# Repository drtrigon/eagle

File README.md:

## Projekte

Results of eagle and kicad CI from travis are stored in https://github.com/drtrigon/eagle/tree/result/pcb branch and linked/shown in https://github.com/drtrigon/sketchbook repo. See there and in [.travis.yml](.travis.yml) for more info.

(might make sense to split projects off into separate repos/submodules)

### N64TinyUSB

Order: make sure to select PCB Thickness 2mm and "Gold Fingers"!

based on boxtec.ch Helvetiny 1.0 PCB design:
* https://github.com/boxtec/helvetiny85
* https://playground.boxtec.ch/doku.php/arduino/attinyusb/helvetiny85

#### code/firmware (design based on attiny45 n64-usb)

Built using the attiny45 n64-usb AVR source files. Works out of the box but emulates 1 device only (that contains both controller).

https://github.com/drtrigon/sketchbook/tree/master/cli/n64dual_tiny45

#### Hint: Order PCB directly

Upload the GERBER files below to https://jlcpcb.com/quote and order.

* Helvetiny85: https://github.com/drtrigon/eagle/blob/master/projects/HelveTiny_1.0_GERBER.zip
* Floweronly Arduino Shield: https://github.com/boxtec/floweronly/blob/master/floweronly_v1.0_GERBER.zip

### Drone_MultiWii / FlightController

### arduino-papilio_1-WireSniffer_Rev1

### DACRackUnit

## Setup

I would like to use features like CI (continous integration) keep a copy/mirror on e.g. github and more.

Maintaining a copy/mirror (more precise: with 2 remotes overloaded origin) on GitHub also allows
to use GitLab and GitHub together and by that all the nice featurs on GitHub.
See also; https://steveperkins.com/migrating-projects-from-github-to-gitlab/

"Option 2: Overload Origin with Both Remotes (needs one single pull/push only)"; in order to clone
and set this repo up use:
```
$ git clone file://///data/mount/gvfs/smb-share:server=.../01git/eagle.git
$ cd eagle
$ git remote set-url --add origin https://github.com/drtrigon/eagle.git
```
you can check the settings with:
```
$ git remote -v
origin  /data/mount/gvfs/smb-share:server=.../01git/eagle.git/ (fetch)
origin  /data/mount/gvfs/smb-share:server=.../01git/eagle.git/ (push)
origin  https://github.com/drtrigon/eagle.git (push)
```

### Enable EDRC.ME for a Repository (for Eagle)
http://www.edrc.me/docs/

### Enable Travis CI for a Repository (for Eagle)
https://github.com/drtrigon/test-eagle-edrc/blob/master/.travis.yml (does not work reliably yet)

Login to Travis-CI using the GitHub account and enable Travis-CI for the given repo.

Add a .travis.yml file to your project, commit, pull/push and enjoy.

A word of caution; the travis run will at the end - if successfull - try to push the
results back to this repo.

### Further Info
EDRC.me: https://michaelblouin.ca/blog/2018/02/25/automate-design-rule-checks-autodesk-eagle/

gerber (travis or local python script): http://www.rocketnumbernine.com/2011/12/14/automating-gerbers-from-eagle
```
...
# create top copper (cmp), bottom copper (sol), top solder mask (stc), bottom solder mask (sts), {top} silkscreen (plc)
${EAGLE} -X -dGERBER_RS274X -o${outputfile}.cmp ${board} Top Pads Vias
${EAGLE} -X -dGERBER_RS274X -o${outputfile}.sol ${board} Bottom Pads Vias
#${EAGLE} -X -dGERBER_RS274X -o${outputfile}.mil ${board} Milling
${EAGLE} -X -dGERBER_RS274X -o${outputfile}.plc ${board} Dimension tPlace tNames
${EAGLE} -X -dGERBER_RS274X -o${outputfile}.stc ${board} tStop
${EAGLE} -X -dGERBER_RS274X -o${outputfile}.sts ${board} bStop
#${EAGLE} -X -dGERBER_RS274X -o${outputfile}.crc ${board} tCream
#${EAGLE} -X -dGERBER_RS274X -o${outputfile}.dpv ${board} Drills
#${EAGLE} -X -dGERBER_RS274X -o${outputfile}.drh ${board} Holes
...
```
(mill and drill needs: gerb274x-mill-drill.cam)

#### Generate schematic, PCB and GERBER from KiCAD (TODO)
* https://forum.kicad.info/t/generate-gerber-files-from-script/1853/15
* https://electronics.stackexchange.com/questions/390135/command-line-interface-for-kicad

## License

The content of this project itself is licensed under the [Creative Commons Attribution 3.0 license](http://creativecommons.org/licenses/by/3.0/us/deed.en_US), and the underlying source code used to format and display that content is licensed under the [MIT license](http://opensource.org/licenses/mit-license.php), see the [LICENSE](LICENSE.md) file for license rights and limitations (MIT).

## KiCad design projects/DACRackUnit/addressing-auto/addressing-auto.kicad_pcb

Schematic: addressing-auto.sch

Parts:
C0, C1, C2, C3, C4: 100nF; C075-032X103
CP0: 10uF; B45181B
CPORT0: DIN-41651-20P
IC0, IC1, IC2, IC3: MC14585; PDIP-16
ICU0: MC14069; PDIP-14
PORT0, PORT1, PORT2, PORT3: DIN-41651-10P
R1, R2, R3, R4, R5, R6, R7, R8, R9, R10, R11, R12, R13, R14, R15, R16: 9k9; 0207_12
SP1: WAGO-3
SW0, SW1, SW2, SW3: 4pins; EDG-04

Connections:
+3V3: C0.1, C1.1, C2.1, C3.1, C4.1, CP0.+, IC0.VDD$16, IC1.VDD$16, IC2.VDD$16, IC3.VDD$16, ICU0.VDD$14, PORT0.P$6, PORT0.P$7, PORT1.P$6, PORT1.P$7, PORT2.P$6, PORT2.P$7, PORT3.P$6, PORT3.P$7, SP1.P$3, SW0.1, SW0.2, SW0.3, SW0.4, SW1.1, SW1.2, SW1.3, SW1.4, SW2.1, SW2.2, SW2.3, SW2.4, SW3.1, SW3.2, SW3.3, SW3.4
+5V: CPORT0.P$2, SP1.P$1
/B0.0: IC0.B0$11, R1.2, SW0.8
/B0.1: IC0.B1$9, R2.2, SW0.7
/B0.2: IC0.B2$1, R3.2, SW0.6
/B0.3: IC0.B3$14, R4.2, SW0.5
/B1.0: IC1.B0$11, R5.2, SW1.8
/B1.1: IC1.B1$9, R6.2, SW1.7
/B1.2: IC1.B2$1, R7.2, SW1.6
/B1.3: IC1.B3$14, R8.2, SW1.5
/B2.0: IC2.B0$11, R9.2, SW2.8
/B2.1: IC2.B1$9, R10.2, SW2.7
/B2.2: IC2.B2$1, R11.2, SW2.6
/B2.3: IC2.B3$14, R12.2, SW2.5
/B3.0: IC3.B0$11, R13.2, SW3.8
/B3.1: IC3.B1$9, R14.2, SW3.7
/B3.2: IC3.B2$1, R15.2, SW3.6
/B3.3: IC3.B3$14, R16.2, SW3.5
/CS: IC0.(A=B)_IN$6, IC1.(A=B)_IN$6, IC2.(A=B)_IN$6, IC3.(A=B)_IN$6, ICU0.OUT6$12
/CS0: IC0.(A=B)_OUT$3, ICU0.IN1$1
/CS0_INV: ICU0.OUT1$2, PORT0.P$1
/CS1: IC1.(A=B)_OUT$3, ICU0.IN2$3
/CS1_INV: ICU0.OUT2$4, PORT1.P$1
/CS2: IC2.(A=B)_OUT$3, ICU0.IN3$5
/CS2_INV: ICU0.OUT3$6, PORT2.P$1
/CS3: IC3.(A=B)_OUT$3, ICU0.IN4$9
/CS3_INV: ICU0.OUT4$8, PORT3.P$1
/CS_INV: CPORT0.P$13, ICU0.IN6$13
/P4: CPORT0.P$8, IC0.A0$10, IC1.A0$10, IC2.A0$10, IC3.A0$10
/P5: CPORT0.P$9, IC0.A1$7, IC1.A1$7, IC2.A1$7, IC3.A1$7
/P6: CPORT0.P$10, IC0.A2$2, IC1.A2$2, IC2.A2$2, IC3.A2$2
/P7: CPORT0.P$11, IC0.A3$15, IC1.A3$15, IC2.A3$15, IC3.A3$15
/RESET_INV: CPORT0.P$4, PORT0.P$9, PORT1.P$9, PORT2.P$9, PORT3.P$9
/SCLK: CPORT0.P$16, PORT0.P$2, PORT1.P$2, PORT2.P$2, PORT3.P$2
/SDIN: CPORT0.P$14, PORT0.P$4, PORT1.P$4, PORT2.P$4, PORT3.P$4
/SDO: CPORT0.P$15, PORT0.P$10, PORT1.P$10, PORT2.P$10, PORT3.P$10
GND: C0.2, C1.2, C2.2, C3.2, C4.2, CP0.-, CPORT0.P$1, IC0.(A<B)_IN$5, IC0.(A>B)_IN$4, IC0.VSS$8, IC1.(A<B)_IN$5, IC1.(A>B)_IN$4, IC1.VSS$8, IC2.(A<B)_IN$5, IC2.(A>B)_IN$4, IC2.VSS$8, IC3.(A<B)_IN$5, IC3.(A>B)_IN$4, IC3.VSS$8, ICU0.IN5$11, ICU0.VSS$7, PORT0.P$5, PORT1.P$5, PORT2.P$5, PORT3.P$5, R1.1, R2.1, R3.1, R4.1, R5.1, R6.1, R7.1, R8.1, R9.1, R10.1, R11.1, R12.1, R13.1, R14.1, R15.1, R16.1, SP1.P$2

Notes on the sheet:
GND
(+5 V)
P0.0
P0.4
P0.5
P0.6
P0.7
SPI CS 0
SPI MOSI (SDO)
SPI MISO (SDI)
SPI CLK (SCLK)
SYNC[inv]
DGND
LDAC[inv]
IOVCC
CLR[inv]
VCC_+5V
VDD_+3.3-4V
(GND = DGND only)
Flachkabel

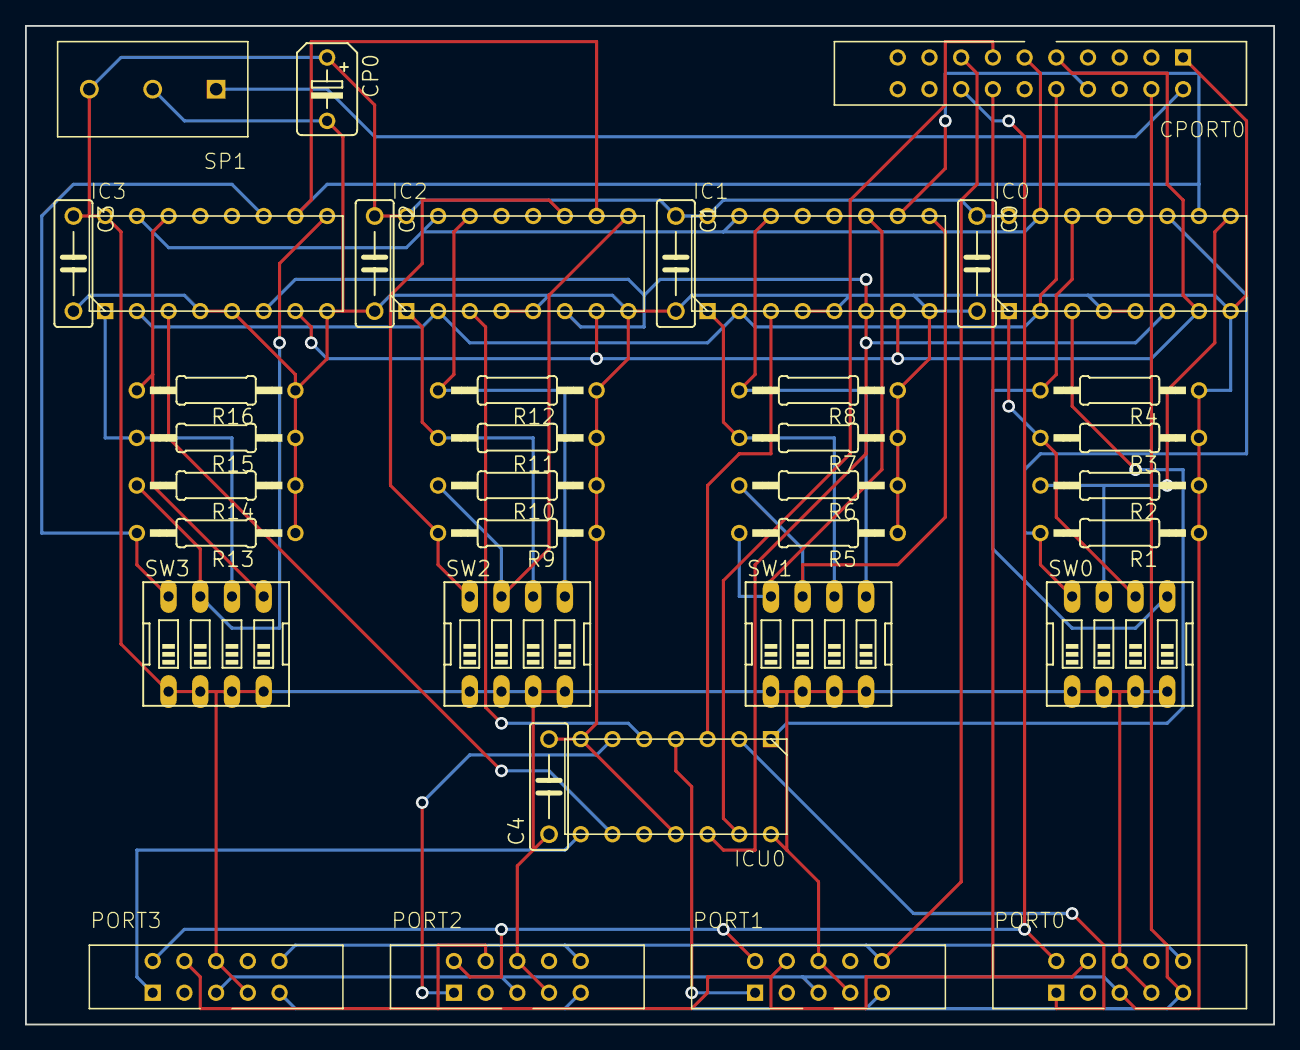
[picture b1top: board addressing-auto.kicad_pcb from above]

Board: 2 copper layers, 100.0 x 80.0 mm, 37 parts (0 on the bottom side), 37 nets.

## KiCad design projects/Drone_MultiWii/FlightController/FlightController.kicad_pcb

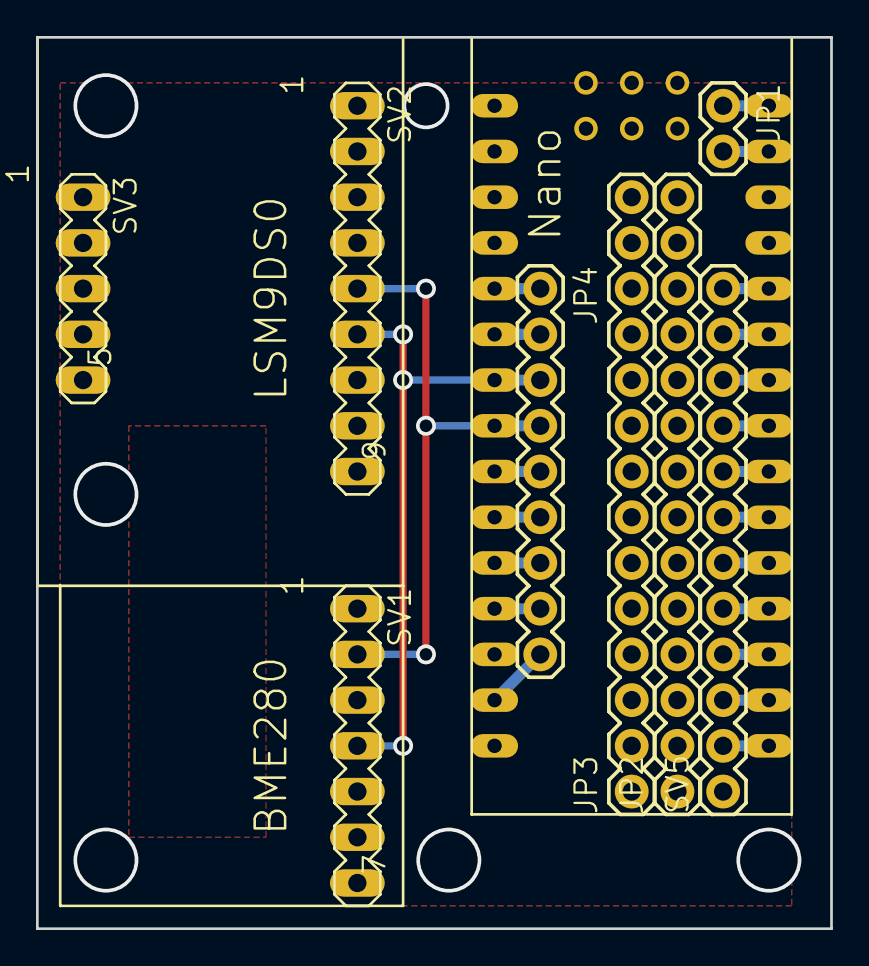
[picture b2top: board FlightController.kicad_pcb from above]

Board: 2 copper layers, 44.1 x 49.5 mm, 9 parts (0 on the bottom side), 24 nets.

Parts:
JP1: M02; 1X02
JP2, JP3: M14; 1X14
JP4: M09; 1X09
SV1: CON1; MA07-1
SV2: CON2; MA09-1
SV3: CON3; MA05-1
SV5: CON5; 1X12
U$1: NANO

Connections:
+5V: JP2.1, JP2.2, JP2.3, JP2.4, JP2.5, JP2.6, JP2.7, JP2.8, JP2.9, JP2.10, JP2.11, JP2.12, JP2.13, JP2.14, SV1.7, SV2.9, U$1.5V
GND: JP3.1, JP3.2, JP3.3, JP3.4, JP3.5, JP3.6, JP3.7, JP3.8, JP3.9, JP3.10, JP3.11, JP3.12, JP3.13, JP3.14, SV1.5, SV2.7, U$1.GND
unnamed: JP1.1, U$1.TX0
unnamed: JP1.2, U$1.RX1
unnamed: JP4.1, U$1.A7
unnamed: JP4.2, U$1.A6
unnamed: JP4.3, SV1.4, SV2.6, U$1.A5
unnamed: JP4.4, SV1.2, SV2.5, U$1.A4
unnamed: JP4.5, U$1.A3
unnamed: JP4.6, U$1.A2
unnamed: JP4.7, U$1.A1
unnamed: JP4.8, U$1.A0
unnamed: JP4.9, U$1.3.3V
unnamed: SV5.2, U$1.D12
unnamed: SV5.3, U$1.D11
unnamed: SV5.4, U$1.D10
unnamed: SV5.5, U$1.D9
unnamed: SV5.6, U$1.D8
unnamed: SV5.7, U$1.D7
unnamed: SV5.8, U$1.D6
unnamed: SV5.9, U$1.D5
unnamed: SV5.10, U$1.D4
unnamed: SV5.11, U$1.D3
unnamed: SV5.12, U$1.D2

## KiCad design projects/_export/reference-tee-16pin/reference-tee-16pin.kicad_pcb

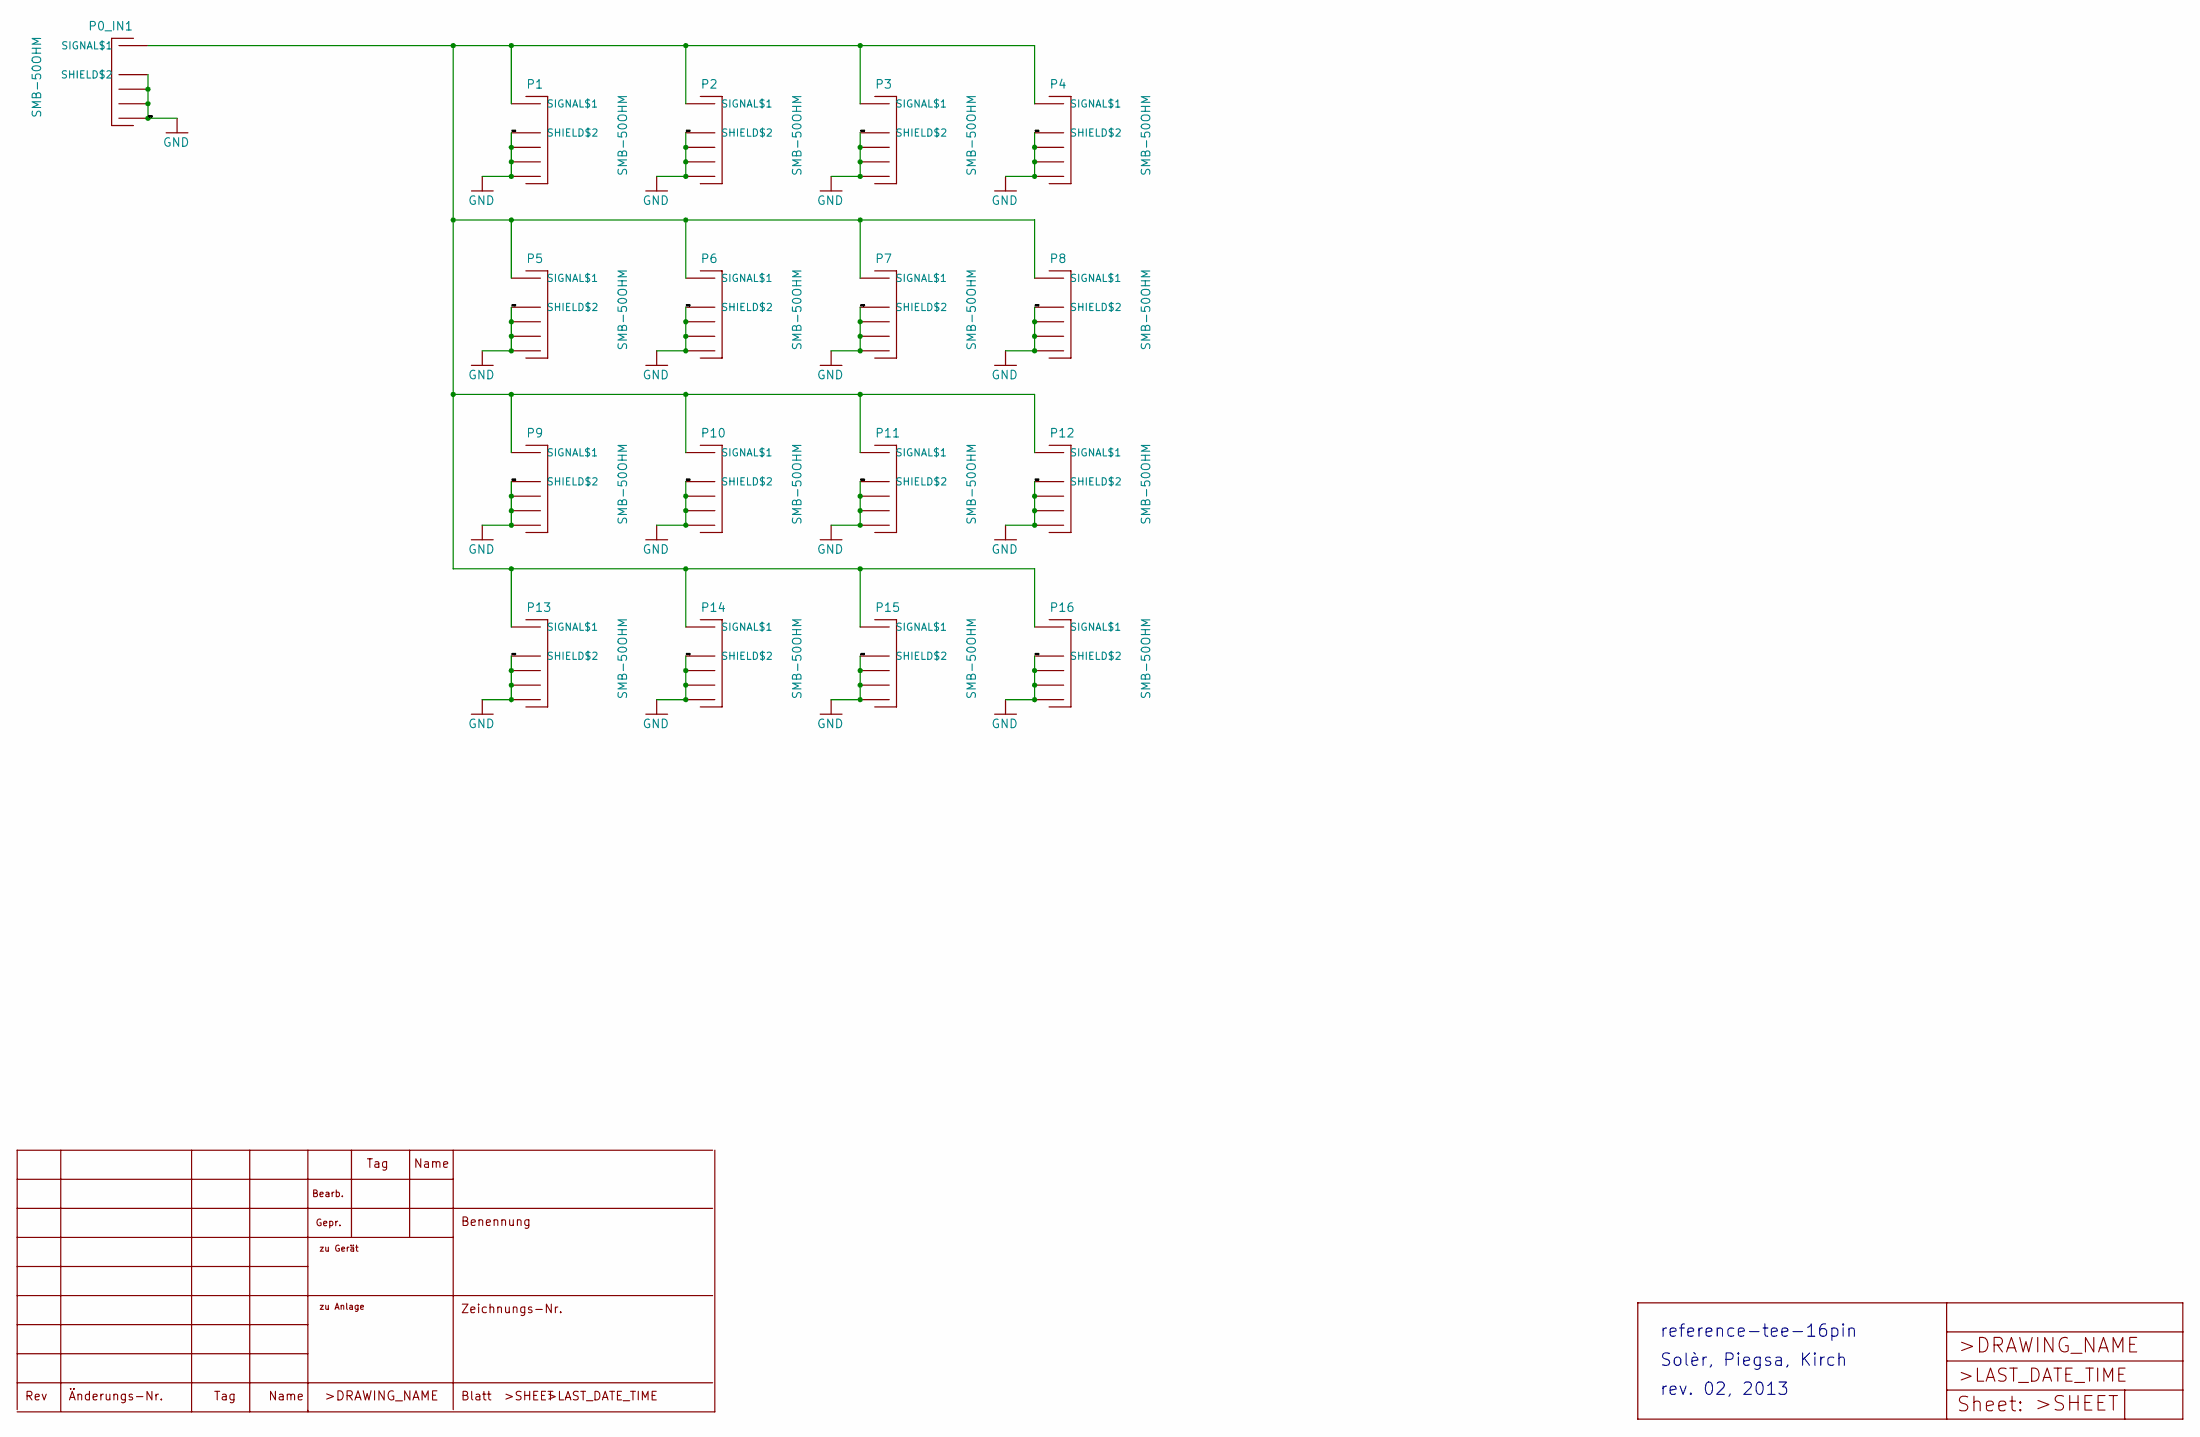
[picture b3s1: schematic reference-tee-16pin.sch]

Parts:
P0_IN1, P1, P2, P3, P4, P5, P6, P7, P8, P9, P10, P11, P12, P13, P14, P15, P16: SMB-50OHM; B-30

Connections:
GND: P0_IN1.P$2 (SHIELD$2), P0_IN1.P$3 (SHIELD$3), P0_IN1.P$4 (SHIELD$4), P0_IN1.P$5 (SHIELD$5), P1.P$2 (SHIELD$2), P1.P$3 (SHIELD$3), P1.P$4 (SHIELD$4), P1.P$5 (SHIELD$5), P2.P$2 (SHIELD$2), P2.P$3 (SHIELD$3), P2.P$4 (SHIELD$4), P2.P$5 (SHIELD$5), P3.P$2 (SHIELD$2), P3.P$3 (SHIELD$3), P3.P$4 (SHIELD$4), P3.P$5 (SHIELD$5), P4.P$2 (SHIELD$2), P4.P$3 (SHIELD$3), P4.P$4 (SHIELD$4), P4.P$5 (SHIELD$5), P5.P$2 (SHIELD$2), P5.P$3 (SHIELD$3), P5.P$4 (SHIELD$4), P5.P$5 (SHIELD$5), P6.P$2 (SHIELD$2), P6.P$3 (SHIELD$3), P6.P$4 (SHIELD$4), P6.P$5 (SHIELD$5), P7.P$2 (SHIELD$2), P7.P$3 (SHIELD$3), P7.P$4 (SHIELD$4), P7.P$5 (SHIELD$5), P8.P$2 (SHIELD$2), P8.P$3 (SHIELD$3), P8.P$4 (SHIELD$4), P8.P$5 (SHIELD$5), P9.P$2 (SHIELD$2), P9.P$3 (SHIELD$3), P9.P$4 (SHIELD$4), P9.P$5 (SHIELD$5), P10.P$2 (SHIELD$2), P10.P$3 (SHIELD$3), P10.P$4 (SHIELD$4), P10.P$5 (SHIELD$5), P11.P$2 (SHIELD$2), P11.P$3 (SHIELD$3), P11.P$4 (SHIELD$4), P11.P$5 (SHIELD$5), P12.P$2 (SHIELD$2), P12.P$3 (SHIELD$3), P12.P$4 (SHIELD$4), P12.P$5 (SHIELD$5), P13.P$2 (SHIELD$2), P13.P$3 (SHIELD$3), P13.P$4 (SHIELD$4), P13.P$5 (SHIELD$5), P14.P$2 (SHIELD$2), P14.P$3 (SHIELD$3), P14.P$4 (SHIELD$4), P14.P$5 (SHIELD$5), P15.P$2 (SHIELD$2), P15.P$3 (SHIELD$3), P15.P$4 (SHIELD$4), P15.P$5 (SHIELD$5), P16.P$2 (SHIELD$2), P16.P$3 (SHIELD$3), P16.P$4 (SHIELD$4), P16.P$5 (SHIELD$5)
unnamed: P0_IN1.P$1 (SIGNAL$1), P1.P$1 (SIGNAL$1), P2.P$1 (SIGNAL$1), P3.P$1 (SIGNAL$1), P4.P$1 (SIGNAL$1), P5.P$1 (SIGNAL$1), P6.P$1 (SIGNAL$1), P7.P$1 (SIGNAL$1), P8.P$1 (SIGNAL$1), P9.P$1 (SIGNAL$1), P10.P$1 (SIGNAL$1), P11.P$1 (SIGNAL$1), P12.P$1 (SIGNAL$1), P13.P$1 (SIGNAL$1), P14.P$1 (SIGNAL$1), P15.P$1 (SIGNAL$1), P16.P$1 (SIGNAL$1)

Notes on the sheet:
reference-tee-16pin
Solèr, Piegsa, Kirch
rev. 02, 2013

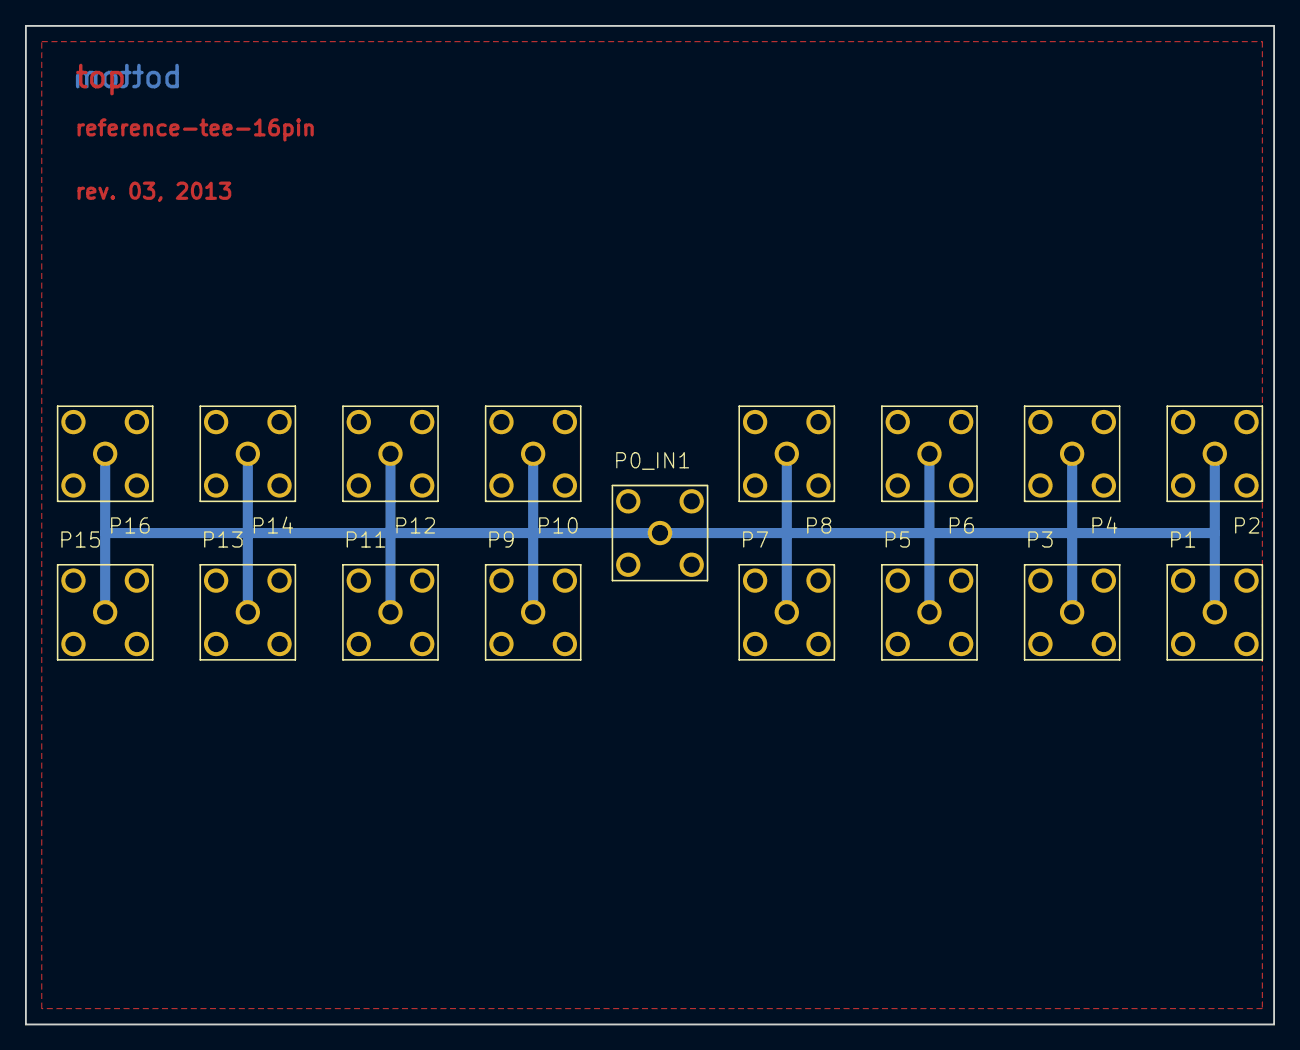
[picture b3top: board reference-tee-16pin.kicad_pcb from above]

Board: 2 copper layers, 100.0 x 80.0 mm, 17 parts (0 on the bottom side), 2 nets.

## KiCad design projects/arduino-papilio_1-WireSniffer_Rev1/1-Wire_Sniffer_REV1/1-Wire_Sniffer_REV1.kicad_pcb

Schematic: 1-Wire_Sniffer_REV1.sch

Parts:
11, 21, 31, 41, 51, 61, 71, 81, 91, 101, 111, 121, 131, 141: LSP10
ANALOG1: PINHD-1X6; 1X06
IC2: SMD-14; SO-14NMW
ICSP1: PINHD-2X3; 2X03
J1, J2, J5: PINHD-1X8TH; 1X08-TH
J3, J4: PINHD-1X10TH; 1X10-TH
J6: PINHD-1X6; 1X06
POWER1: PINHD-1X8TH; 1X08-TH
R1: R-EU_0207/10; 0207_10
RESET1: 10-XX; B3F-10XX
SV1: MA10-2
SV2: MA08-1
U$1: DISCLAIMER
X1: RJ452-B; RJ45-SHIELD2
X3: W237-102

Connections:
+5V: ICSP1.2, J2.5, POWER1.5, R1.2
/MISO: ICSP1.1
/MOSI: ICSP1.4
/RESET: ICSP1.5, J2.3, POWER1.3, RESET1.3, RESET1.4 (P1), SV1.19
/SCK: ICSP1.3
GND: ICSP1.6, J2.6, J2.7, J3.7, J4.7, POWER1.6, POWER1.7, RESET1.1 (S), RESET1.2 (S1), SV1.17, SV2.5, X1.5, X3.1
unnamed: 11.MP, IC2.P$1
unnamed: 21.MP, IC2.P$2
unnamed: 31.MP, IC2.P$3
unnamed: 41.MP, IC2.P$4
unnamed: 51.MP, IC2.P$5
unnamed: 61.MP, IC2.P$6
unnamed: 71.MP, IC2.P$7
unnamed: 81.MP, IC2.P$8
unnamed: 91.MP, IC2.P$9
unnamed: 101.MP, IC2.P$10
unnamed: 111.MP, IC2.P$11
unnamed: 121.MP, IC2.P$12
unnamed: 131.MP, IC2.P$13
unnamed: 141.MP, IC2.P$14
unnamed: ANALOG1.1, J6.1
unnamed: ANALOG1.2, J6.2
unnamed: ANALOG1.3, J6.3
unnamed: ANALOG1.4, J6.4
unnamed: ANALOG1.5, J6.5
unnamed: ANALOG1.6, J6.6
unnamed: J1.1, J5.1, SV1.1
unnamed: J1.2, J5.2, SV1.3
unnamed: J1.3, J5.3, SV1.5
unnamed: J1.4, J5.4, SV1.7
unnamed: J1.5, J5.5, SV1.9
unnamed: J1.6, J5.6, SV1.11
unnamed: J1.7, J5.7, SV1.13
unnamed: J1.8, J5.8, SV1.15
unnamed: J2.1, POWER1.1
unnamed: J2.2, POWER1.2
unnamed: J2.4, POWER1.4
unnamed: J2.8, POWER1.8
unnamed: J3.1, J4.1
unnamed: J3.2, J4.2
unnamed: J3.3, J4.3
unnamed: J3.4, J4.4
unnamed: J3.5, J4.5
unnamed: J3.6, J4.6
unnamed: J3.8, J4.8
unnamed: J3.9, J4.9
unnamed: J3.10, J4.10
unnamed: R1.1, SV1.20
unnamed: SV1.2, SV1.4, SV1.6, SV1.8, SV1.10, SV1.12, SV1.14, SV1.16, SV1.18, SV2.4, X1.4, X3.2
unnamed: SV2.1, X1.1
unnamed: SV2.2, X1.2
unnamed: SV2.3, X1.3
unnamed: SV2.6, X1.6
unnamed: SV2.7, X1.7
unnamed: SV2.8, X1.8

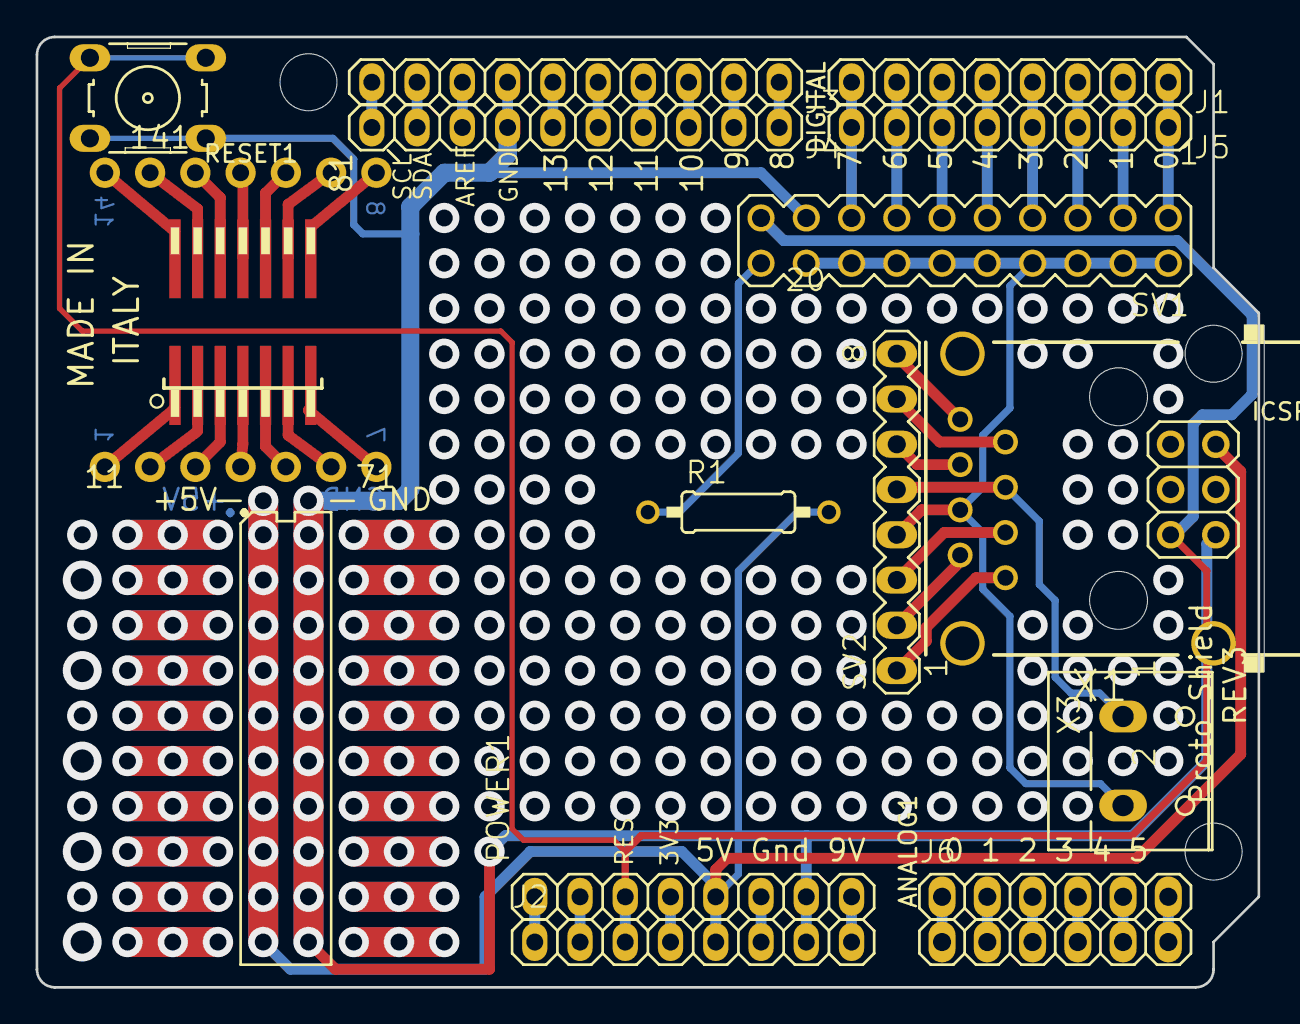
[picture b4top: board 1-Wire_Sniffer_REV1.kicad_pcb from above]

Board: 2 copper layers, 68.6 x 53.3 mm, 34 parts (0 on the bottom side), 52 nets.

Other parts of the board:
@HOLE0, @HOLE1, @HOLE2: (no value)

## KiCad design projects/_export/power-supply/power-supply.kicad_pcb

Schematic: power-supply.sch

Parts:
C0, C1, C2, C3, C11, C12, C21, C22: 100nF; C050-025X075
CP0, CP1, CP11, CP12, CP21, CP22: 10uF; B45181B
CP2, CP31: 2.2uF; B45181B
IC1, IC2: LM317; 317TS
IC3: VREF-REF02-MAX6350; PDIP-8
PP0: WAGO-3
R1, R2: 1k; RTRIM3296Y
RP0: SMB-50OHM; B-30
SP0, SP1: WAGO-3

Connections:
+3V3: C21.1, C22.1, CP21.+, CP22.+, IC2.2 (OUT), R2.1 (A), SP1.P$3
+5V: C11.1, C12.1, CP11.+, CP12.+, IC1.2 (OUT), R1.1 (A), SP1.P$1
+5V/1: CP31.+, IC3.V_OUT$6 (V_OUT$5), RP0.P$1 (SIGNAL$1)
+15V: C1.1, C2.1, C3.1, CP1.+, CP2.+, IC1.3 (IN), IC2.3 (IN), IC3.V_IN$2, PP0.P$1, SP0.P$1
-15V: C0.2, CP0.-, PP0.P$3, SP0.P$3
GND: C0.1, C1.2, C2.2, C3.2, C11.2, C12.2, C21.2, C22.2, CP0.+, CP1.-, CP2.-, CP11.-, CP12.-, CP21.-, CP22.-, CP31.-, IC3.GND$4, PP0.P$2, R1.3 (E), R2.3 (E), RP0.P$2 (SHIELD$2), RP0.P$3 (SHIELD$3), RP0.P$4 (SHIELD$4), RP0.P$5 (SHIELD$5), SP0.P$2, SP1.P$2
unnamed: IC1.1 (ADJ), R1.2 (S)
unnamed: IC2.1 (ADJ), R2.2 (S)

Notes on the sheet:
VDD_+15V
AGND
VSS_-15V
VCC_+5V
DGND
VDD_+3.3-4V
VREF
connect AGND and DGND at ONE (~) point
power-supply
Solèr, Piegsa, Kirch
rev. 04, 2013

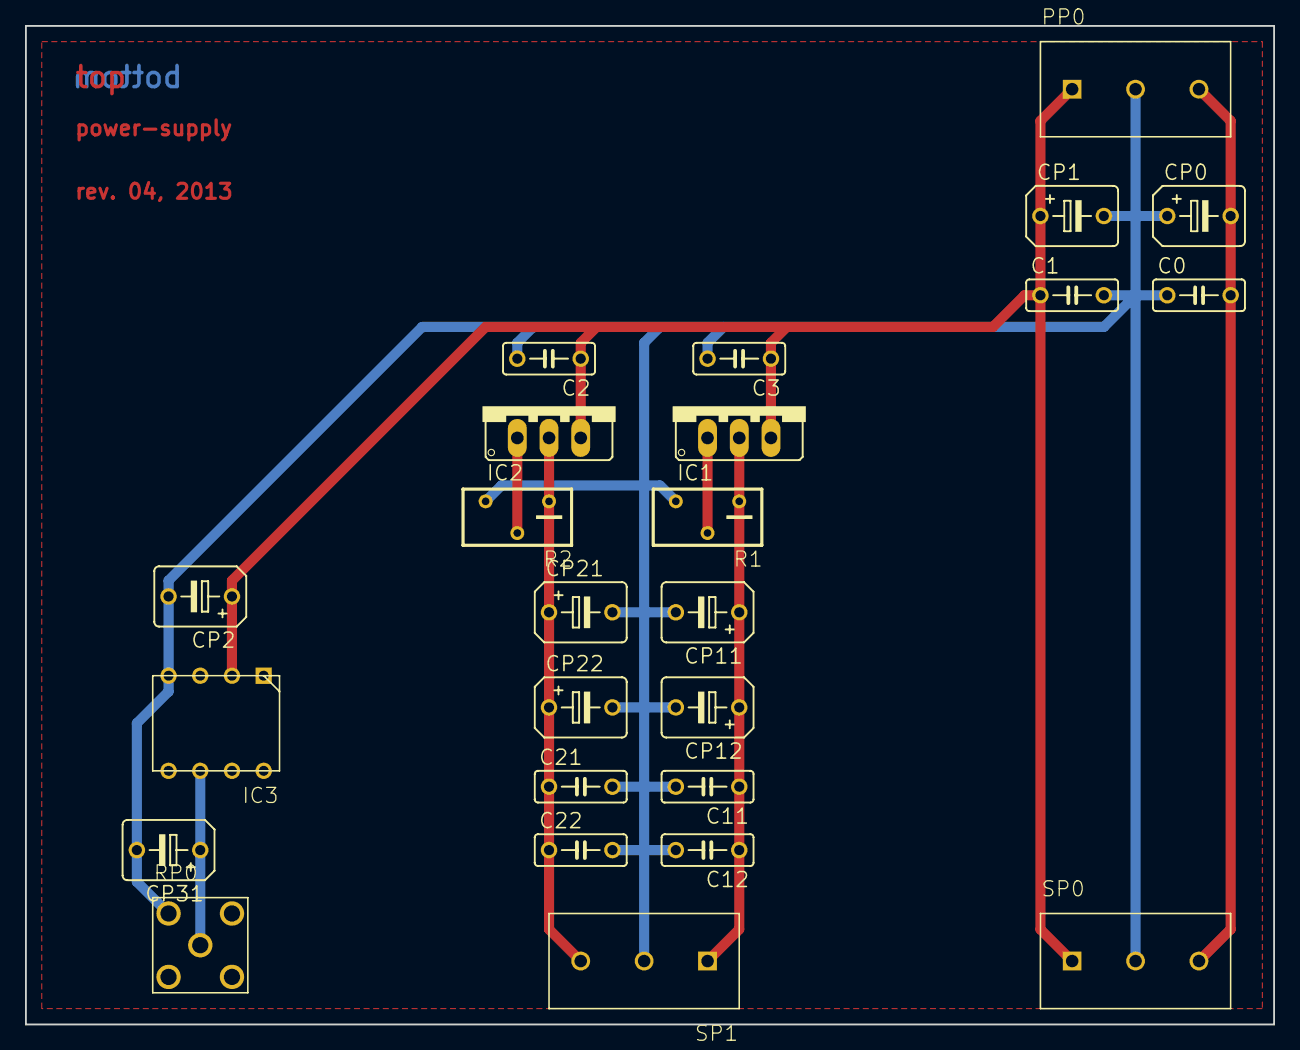
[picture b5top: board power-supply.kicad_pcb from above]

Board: 2 copper layers, 100.0 x 80.0 mm, 25 parts (0 on the bottom side), 8 nets.

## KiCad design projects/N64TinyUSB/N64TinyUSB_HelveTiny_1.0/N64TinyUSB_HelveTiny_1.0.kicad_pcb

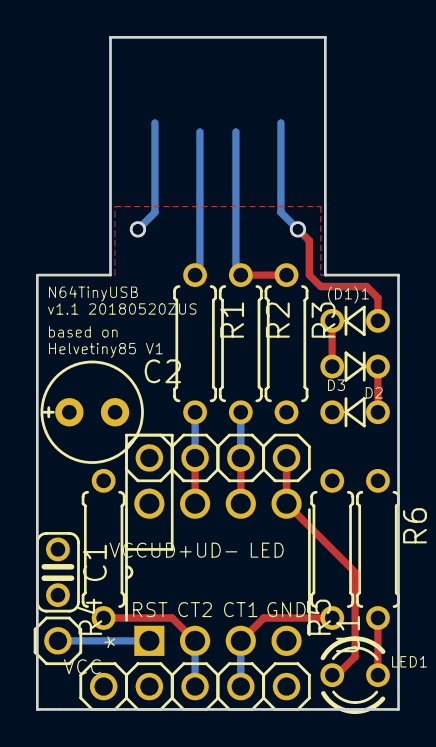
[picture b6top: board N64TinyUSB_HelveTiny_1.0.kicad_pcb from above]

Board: 2 copper layers, 20.1 x 37.3 mm, 24 parts (0 on the bottom side), 14 nets.

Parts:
(D1)1: 1N4150; D-2.5
C1: 0.1μF; C025-024X044
C2: 4u7; E2,5-6E
CTRL1: pin3; 1X01
CTRL2: pin2; 1X01
D2, D3: 1N4150; D-2.5
D+1: pin7; 1X01
D-1: pin6; 1X01
DUMMY1: pin; 1X01
GND1: pin4; 1X01
JP1: USBPCB; USB-A-PCB
LED1: red; LED3MM
LED2: pin5; 1X01
R1, R2: 22/68; 0207_7
R3: 1.5K; 0207_7
R4, R5, R6: 1K; 0207_7
RST1: pin1; 1X01
U1: ATTINY85-20PU; DIP254P762X533-8
VCC1, VCC2: pin; 1X01

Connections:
GND: C1.2, C2.-, GND1.1, JP1.GND, R6.1, U1.4
unnamed: (D1)1.A, JP1.5V
unnamed: (D1)1.C, D2.A
unnamed: CTRL1.1, R5.1, U1.3
unnamed: CTRL2.1, R4.1, U1.2
unnamed: D2.C, D3.A
unnamed: D+1.1, R1.2, U1.7
unnamed: D-1.1, R2.2, U1.6
unnamed: JP1.USB_M, R2.1, R3.1
unnamed: JP1.USB_P, R1.1
unnamed: LED1.A, LED2.1, U1.5
unnamed: LED1.K, R6.2
unnamed: RST1.1, U1.1
VCC: C1.1, C2.+, D3.C, R3.2, R4.2, R5.2, U1.8, VCC1.1, VCC2.1

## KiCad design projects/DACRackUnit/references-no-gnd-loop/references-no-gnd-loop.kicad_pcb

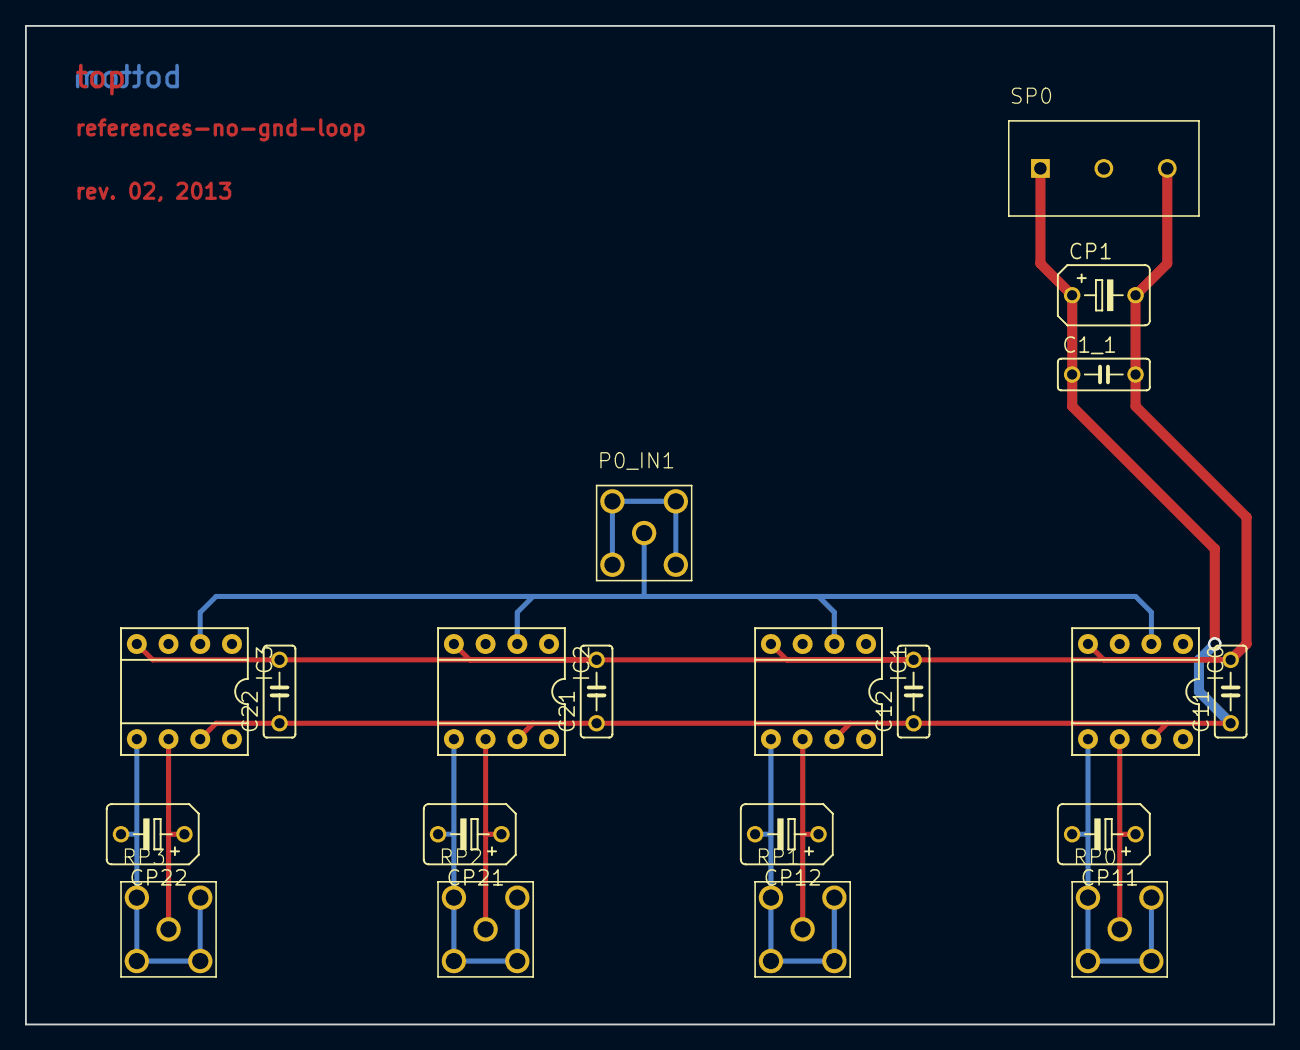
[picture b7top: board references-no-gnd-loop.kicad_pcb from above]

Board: 2 copper layers, 100.0 x 80.0 mm, 20 parts (0 on the bottom side), 12 nets.

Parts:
C1_1, C11, C12, C21, C22: 100nF; C050-025X075
CP1: 10uF; B45181B
CP11, CP12, CP21, CP22: 2.2uF; B45181B
IC0, IC1, IC2, IC3: INA118P; DIL08
P0_IN1: SMB-50OHM; B-30
RP0, RP1, RP2, RP3: SMB-50OHM; B-30
SP0: WAGO-3

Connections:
+15V: C1_1.1, C11.1, C12.1, C21.1, C22.1, CP1.+, IC0.7, IC1.7, IC2.7, IC3.7, SP0.P$1
-15V: C1_1.2, C11.2, C12.2, C21.2, C22.2, CP1.-, IC0.4, IC1.4, IC2.4, IC3.4, SP0.P$3
/RGND0: CP11.-, IC0.5, RP0.P$2, RP0.P$3, RP0.P$4, RP0.P$5
/RGND1: CP12.-, IC1.5, RP1.P$2, RP1.P$3, RP1.P$4, RP1.P$5
/RGND2: CP21.-, IC2.5, RP2.P$2, RP2.P$3, RP2.P$4, RP2.P$5
/RGND3: CP22.-, IC3.5, RP3.P$2, RP3.P$3, RP3.P$4, RP3.P$5
/VOUT0: CP11.+, IC0.6, RP0.P$1
/VOUT1: CP12.+, IC1.6, RP1.P$1
/VOUT2: CP21.+, IC2.6, RP2.P$1
/VOUT3: CP22.+, IC3.6, RP3.P$1
GND: IC0.3, IC1.3, IC2.3, IC3.3, P0_IN1.P$2, P0_IN1.P$3, P0_IN1.P$4, P0_IN1.P$5
unnamed: IC0.2, IC1.2, IC2.2, IC3.2, P0_IN1.P$1

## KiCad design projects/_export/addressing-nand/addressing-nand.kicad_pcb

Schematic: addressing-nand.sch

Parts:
C0, C1, C2, C3, C4: 100nF; C050-025X075
CP0: 10uF; B45181B
CPORT0: DIN-41651-20P
IC0, IC1, IC2, IC3: MC14585; PDIP-16
IC4: 4011N; DIL14
LED0, LED1, LED2, LED3: 2mA (max); LED3MM
PORT0, PORT1, PORT2, PORT3: DIN-41651-10P
R0, R1, R2, R3: 1k-2k; 0207_2V
RN0, RN1, RN2, RN3: 9k9; RN-6
SP1: WAGO-3
SW0, SW1, SW2, SW3: 4pins; EDG-04
T0_A1: BS250; SOT54E
T0_B1: BS170; SOT54E

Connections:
+3V3: C0.1, C1.1, C2.1, C3.1, C4.1, CP0.+, IC0.(A=B)_IN$6, IC0.VDD$16, IC1.(A=B)_IN$6, IC1.VDD$16, IC2.(A=B)_IN$6, IC2.VDD$16, IC3.(A=B)_IN$6, IC3.VDD$16, IC4.14 (VDD), PORT0.P$6, PORT0.P$7, PORT1.P$6, PORT1.P$7, PORT2.P$6, PORT2.P$7, PORT3.P$6, PORT3.P$7, SP1.P$3, SW0.1, SW0.2, SW0.3, SW0.4, SW1.1, SW1.2, SW1.3, SW1.4, SW2.1, SW2.2, SW2.3, SW2.4, SW3.1, SW3.2, SW3.3, SW3.4, T0_A1.S
+5V: CPORT0.P$2, SP1.P$1
/B0.0: IC0.B0$11, RN0.6, SW0.8
/B0.1: IC0.B1$9, RN0.5, SW0.7
/B0.2: IC0.B2$1, RN0.4, SW0.6
/B0.3: IC0.B3$14, RN0.3, SW0.5
/B1.0: IC1.B0$11, RN1.6, SW1.8
/B1.1: IC1.B1$9, RN1.5, SW1.7
/B1.2: IC1.B2$1, RN1.4, SW1.6
/B1.3: IC1.B3$14, RN1.3, SW1.5
/B2.0: IC2.B0$11, RN2.6, SW2.8
/B2.1: IC2.B1$9, RN2.5, SW2.7
/B2.2: IC2.B2$1, RN2.4, SW2.6
/B2.3: IC2.B3$14, RN2.3, SW2.5
/B3.0: IC3.B0$11, RN3.6, SW3.8
/B3.1: IC3.B1$9, RN3.5, SW3.7
/B3.2: IC3.B2$1, RN3.4, SW3.6
/B3.3: IC3.B3$14, RN3.3, SW3.5
/CS: IC4.1 (I0), IC4.5 (I0), IC4.8 (I0), IC4.12 (I0), T0_A1.D, T0_B1.D
/CS0: IC0.(A=B)_OUT$3, IC4.2 (I1), R0.2
/CS0_INV: IC4.3 (O), PORT0.P$1
/CS1: IC1.(A=B)_OUT$3, IC4.6 (I1), R1.2
/CS1_INV: IC4.4 (O), PORT1.P$1
/CS2: IC2.(A=B)_OUT$3, IC4.9 (I1), R2.2
/CS2_INV: IC4.10 (O), PORT2.P$1
/CS3: IC3.(A=B)_OUT$3, IC4.13 (I1), R3.2
/CS3_INV: IC4.11 (O), PORT3.P$1
/CS_INV: CPORT0.P$13, T0_A1.G, T0_B1.G
/P4: CPORT0.P$8, IC0.A0$10, IC1.A0$10, IC2.A0$10, IC3.A0$10
/P5: CPORT0.P$9, IC0.A1$7, IC1.A1$7, IC2.A1$7, IC3.A1$7
/P6: CPORT0.P$10, IC0.A2$2, IC1.A2$2, IC2.A2$2, IC3.A2$2
/P7: CPORT0.P$11, IC0.A3$15, IC1.A3$15, IC2.A3$15, IC3.A3$15
/RESET_INV: CPORT0.P$4, PORT0.P$9, PORT1.P$9, PORT2.P$9, PORT3.P$9
/SCLK: CPORT0.P$16, PORT0.P$2, PORT1.P$2, PORT2.P$2, PORT3.P$2
/SDIN: CPORT0.P$14, PORT0.P$4, PORT1.P$4, PORT2.P$4, PORT3.P$4
/SDO: CPORT0.P$15, PORT0.P$10, PORT1.P$10, PORT2.P$10, PORT3.P$10
GND: C0.2, C1.2, C2.2, C3.2, C4.2, CP0.-, CPORT0.P$1, IC0.(A<B)_IN$5, IC0.(A>B)_IN$4, IC0.VSS$8, IC1.(A<B)_IN$5, IC1.(A>B)_IN$4, IC1.VSS$8, IC2.(A<B)_IN$5, IC2.(A>B)_IN$4, IC2.VSS$8, IC3.(A<B)_IN$5, IC3.(A>B)_IN$4, IC3.VSS$8, IC4.7 (VSS), LED0.K (C), LED1.K (C), LED2.K (C), LED3.K (C), PORT0.P$5, PORT1.P$5, PORT2.P$5, PORT3.P$5, RN0.1, RN0.2, RN1.1, RN1.2, RN2.1, RN2.2, RN3.1, RN3.2, SP1.P$2, T0_B1.S
unnamed: LED0.A, R0.1
unnamed: LED1.A, R1.1
unnamed: LED2.A, R2.1
unnamed: LED3.A, R3.1

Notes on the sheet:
GND
(+5 V)
P0.0
P0.4
P0.5
P0.6
P0.7
SPI CS 0
SPI MOSI (SDO)
SPI MISO (SDI)
SPI CLK (SCLK)
SYNC[inv]
DGND
LDAC[inv]
IOVCC
CLR[inv]
VCC_+5V
VDD_+3.3-4V
(GND = DGND only)
Flachkabel
addressing-nand
Solèr, Piegsa, Kirch
rev. 02, 2013

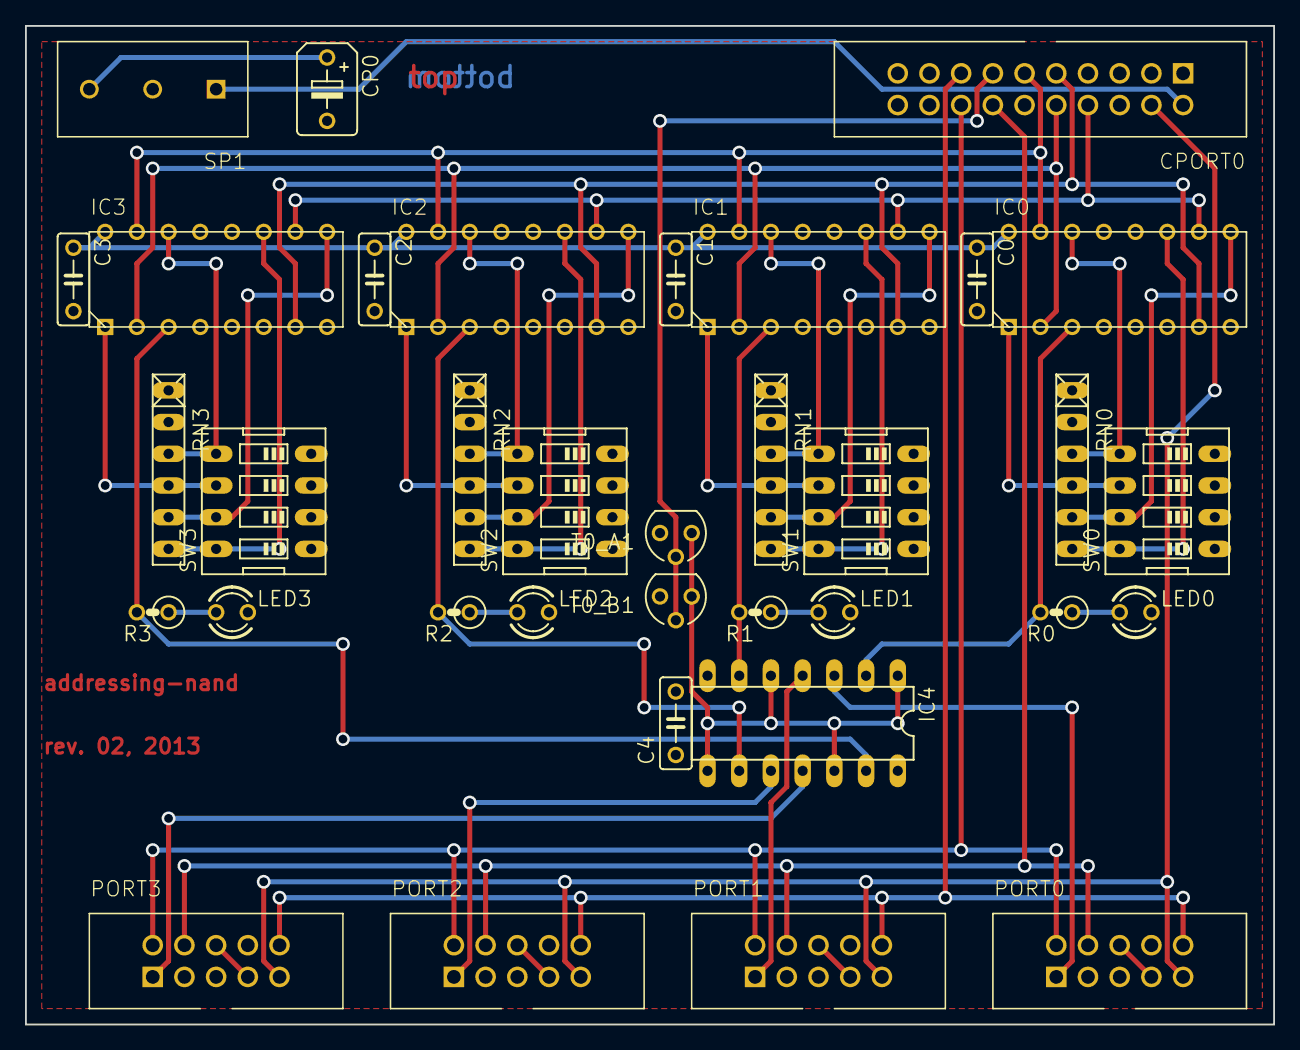
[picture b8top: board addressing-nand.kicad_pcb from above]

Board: 2 copper layers, 100.0 x 80.0 mm, 35 parts (0 on the bottom side), 41 nets.
